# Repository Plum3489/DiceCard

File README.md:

# DiceCard

A buisiness-card-sized, battery-powered electronic dice roller :D 
Its build around the **ATtiny1614-SSN**, 10 LEDs, and a single button. 

## Instructions
1. Press to wake
2. short-press to pick a die
3. hold to roll
It goes back to sleep when it's done.

## Features

- 7 selectable dice  **d2, d4, d6, d8, d10**, plus two special modes:
  - **"1" -> d20**: two chained d10 rolls, LED-animated, you sum the results
  - **"9" -> d100**: tens-digit roll + units-digit roll (flat 1-100)
  - Deep sleep (power-down) between uses -> wakes only on button press
  - Only a single button

## Bill of materials (BOM)
| Amount | Part                        | Notes                                             | Price          | Links                                                                                                                                                                                                                                                                                                       |   |   |   |   |   |
|--------|-----------------------------|---------------------------------------------------|----------------|-------------------------------------------------------------------------------------------------------------------------------------------------------------------------------------------------------------------------------------------------------------------------------------------------------------|---|---|---|---|---|
| 1x     | ATtiny1614                  |                                                   | 1,05€          | https://www.reichelt.de/de/de/shop/produkt/8-bit-attiny_avr-risc_mikrocontroller_16_kb_20_mhz_soic-14-335590#closemodal                                                                                                                                                                                     |   |   |   |   |   |
| 1x     | Cap 0805, 1 µF              |                                                   | 0,08€          | https://www.reichelt.de/de/de/shop/produkt/mlcc_0805_1_f_16_v_x7r_-10_h1_25_mm-429214                                                                                                                                                                                                                       |   |   |   |   |   |
| 10x    | LED, SMD 0603 Red           |                                                   | 0,07€          | https://www.reichelt.de/de/de/shop/produkt/led_smd_0603_rot_56_mcd_100_-231657                                                                                                                                                                                                                              |   |   |   |   |   |
| 10x    | Resistor, SMD 0402 2,2 kOhm |                                                   | 0,02€          | https://www.reichelt.de/de/de/shop/produkt/smd-widerstand_0402_2_2_kohm_63_mw_1_-182934                                                                                                                                                                                                                     |   |   |   |   |   |
| 1x     | Cap 1206 100nF              |                                                   | 0,04€          | https://www.reichelt.de/de/de/shop/produkt/mlcc_1206_100_nf_100_v_-10_x7r-409241                                                                                                                                                                                                                            |   |   |   |   |   |
| 1x     | Battery Holder Ø 20 mm      |                                                   | 0,67€          | https://www.reichelt.de/de/de/shop/produkt/knopfzellenclip_fuer_20_mm_smd-74686                                                                                                                                                                                                                             |   |   |   |   |   |
| 1x     | UDPI-Programming Board      | IF NEEDED. ONLY ONE. YOU DONT NEED THEM PER BOARD | 7,50€          | https://www.berrybase.de/adafruit-updi-friend-3v-5v-stromversorgung-ch340e-chip-usb-c-3v-5v-1k-rueckkopplungswiderstand?gad_source=1&gad_campaignid=22696911352&gbraid=0AAAAADSQJK6ArylTule_RzYSf8CoHO8D9&gclid=CjwKCAjwqJXUBhBNEiwA8BgG7k4nVT0fIzVh1WPstvDr96SSSF5Iflz-FT8h6PRQLShXnonjbpDu8xoCaoEQAvD_BwE |   |   |   |   |   |
| 1x     | PCB                         |                                                   | ~4€            |                                                                                                                                                                                                                                                                                                             |   |   |   |   |   |
| Total  | ----------                  | ----------                                        | 6,74€ (+7,50€) |                                                                                                                                                                                                                                                                                                             |   |   |   |   |   |

## Pin Map
| Silkscreen label | ATtiny1614 pin | Function |
|---|---|---|
| D1 | PA2 | LED |
| D2 | PA3 | LED |
| D3 | PA4 | LED |
| D4 | PA5 | LED |
| D5 | PA6 | LED |
| D6 | PA7 | LED |
| D7 | PB3 | LED |
| D8 | PB2 | LED |
| D9 | PB1 | LED |
| D10 | PB0 | LED |
| — | PA1 | Button (to GND, internal pull-up) |
| — | PA0 | UPDI (programming only) |
| — | VCC | CR2032 + |
| — | GND | CR2032 − |

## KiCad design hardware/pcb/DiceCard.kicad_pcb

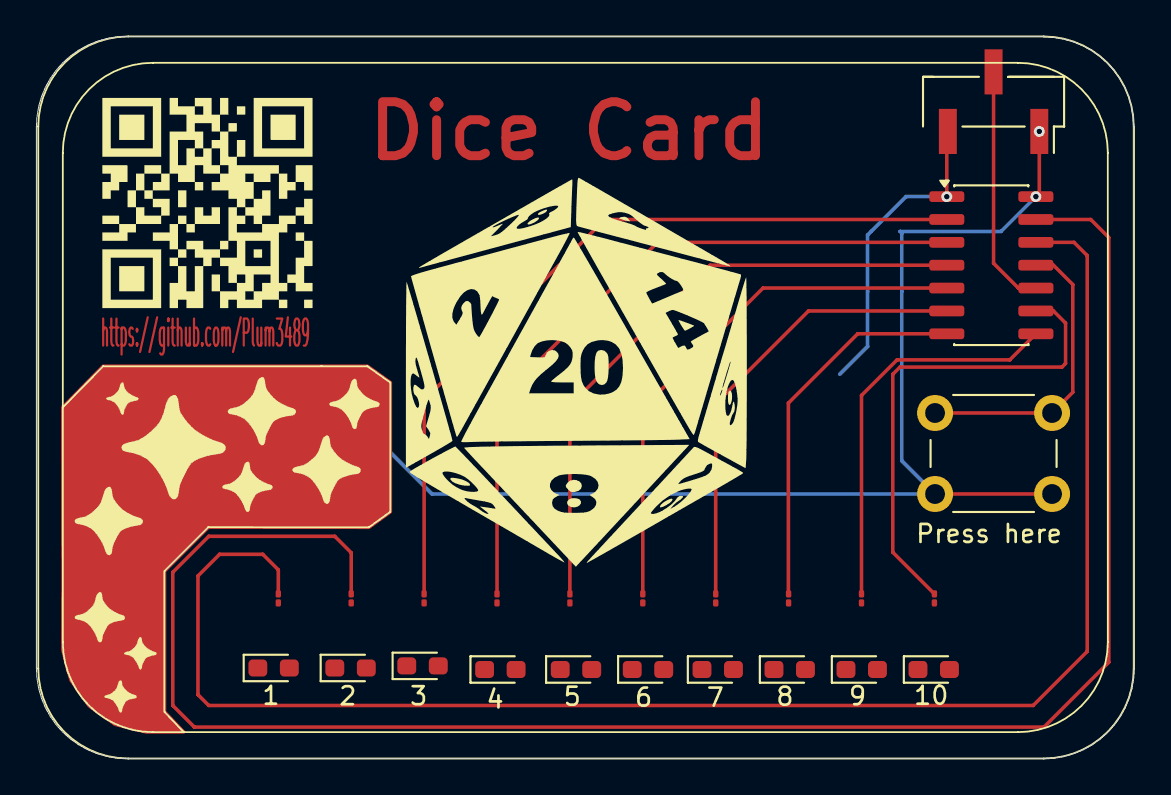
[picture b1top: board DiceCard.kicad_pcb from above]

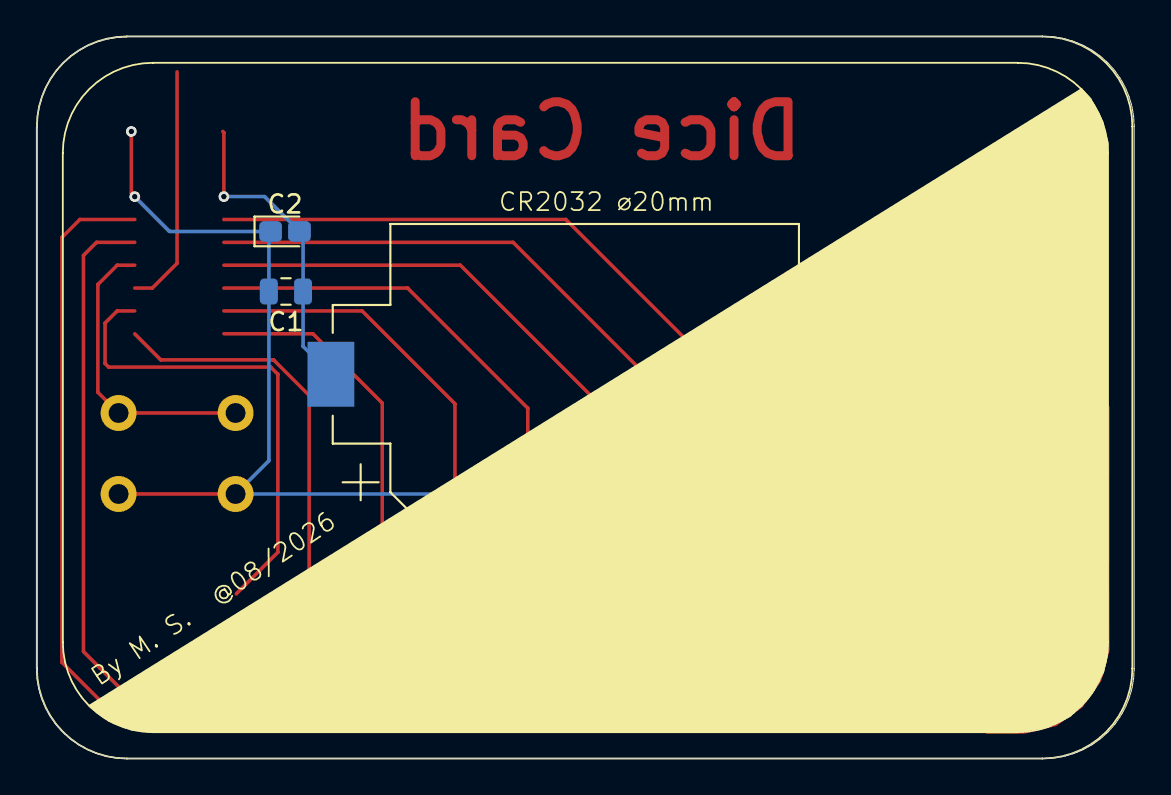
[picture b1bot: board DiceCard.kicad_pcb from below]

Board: 2 copper layers, 61.0 x 40.1 mm, 26 parts (3 on the bottom side), 24 nets.

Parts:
1, 2, 3, 4, 5, 6, 7, 8, 9, 10: LED; LED_0603_1608Metric_Pad1.05x0.95mm_HandSolder
BT1: Battery_Cell; BatteryHolder_Keystone_1060_1x2032
C1: 100nF; C_0805_2012Metric
C2: 1µF; CP_EIA-1608-08_AVX-J_HandSolder
J1: Conn_01x03_Pin; PinHeader_1x03_P2.54mm_Vertical_SMD_Pin1Right
Press here: SW_Push; SW_PUSH_6mm
R1, R2, R3, R4, R5, R6, R7, R8, R9, R10: 2.2kΩ; R_01005_0402Metric
U1: ATtiny1614-SS; SOIC-14_3.9x8.7mm_P1.27mm

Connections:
unnamed: BT1.1 (+), C1.1, C2.2, J1.3, U1.1 (VCC)
unnamed: 1.1 (K), 2.1 (K), 3.1 (K), 4.1 (K), 5.1 (K), 6.1 (K), 7.1 (K), 8.1 (K), 9.1 (K), 10.1 (K), BT1.2 (-), C1.2, C2.1, J1.1, Press here.2, U1.14 (GND)
unnamed: 1.2 (A), R1.2
unnamed: 2.2 (A), R2.2
unnamed: 3.2 (A), R3.2
unnamed: 4.2 (A), R4.2
unnamed: 5.2 (A), R5.2
unnamed: 6.2 (A), R6.2
unnamed: 7.2 (A), R7.2
unnamed: 8.2 (A), R8.2
unnamed: 9.2 (A), R9.2
unnamed: 10.2 (A), R10.2
unnamed: J1.2, U1.10 (~RESET/PA0)
unnamed: Press here.1, U1.11 (PA1)
unnamed: R1.1, U1.12 (PA2)
unnamed: R2.1, U1.13 (PA3)
unnamed: R3.1, U1.2 (PA4)
unnamed: R4.1, U1.3 (PA5)
unnamed: R5.1, U1.4 (PA6)
unnamed: R6.1, U1.5 (PA7)
unnamed: R10.1, U1.9 (PB0)
unnamed: R9.1, U1.8 (PB1)
unnamed: R8.1, U1.7 (PB2)
unnamed: R7.1, U1.6 (PB3)

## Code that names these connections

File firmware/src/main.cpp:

/*
      DiceCard - ATtiny1614-SSN
-------------------------------------

Code for my Dice Card, first time using the chip itself instead of a microcontroller board :P

PIN MAP:
    D1  = PA2      D6  = PA7
    D2  = PA3      D7  = PB3
    D3  = PA4      D8  = PB2
    D4  = PA5      D9  = PB1
    D5  = PA6      D10 = PB0
    Button = PA1 (button to GND, internal pull-up, active LOW)
    PA0 = UPDI (not used as GPIO)
*/




#include <Arduino.h>
#include <avr/sleep.h>
#include <avr/interrupt.h>

#define D100_TENS_UNITS METHOD true

const uint16_t LONG_PRESS_MS = 550;
const uint16_t DEBOUNCE_MS = 25;

// Pins
const uint8_t ledPins[10] = {
  PIN_PA2, // D1
  PIN_PA3, // D2
  PIN_PA4, // D3
  PIN_PA5, // D4
  PIN_PA6, // D5
  PIN_PA7, // D6
  PIN_PB3, // D7
  PIN_PB2, // D8
  PIN_PB1, // D9
  PIN_PB0  // D10
};
const uint8_t BTN = PIN_PA1;

// Selectable Die
const uint8_t dieOptions[7] = {1, 2, 4, 6, 8, 9, 10};
const uint8_t NUM_OPTIONS = 7;

// Methods

void allOff(){
  for(uint16_t i = 0; i<10; i++) digitalWrite(ledPins[i], LOW);
}

void allOn(){
  for(uint16_t i = 0; i<10; i++) digitalWrite(ledPins[i], HIGH);
}

void lightOnly(uint8_t idx){
  for (uint8_t i = 0; i < 10; i++) digitalWrite(ledPins[i], i == idx ? HIGH : LOW);
}

bool buttonPressed(){
  return digitalRead(BTN) == LOW;
}

void waitForPressStart(){ while (!buttonPressed()) { /* spin */ }
  delay(DEBOUNCE_MS);
  while (!buttonPressed()) { /* debounce glitch, keep waiting */ }
}

// Blocks until either the button is released before LONG_PRESS MS -> returns false
// or the hold time reaches LONG_PRESS_MS -> returns true immediately
bool waitForPressOutcome() {
  waitForPressStart();
  uint32_t start = millis();
  while (buttonPressed()) {
    if (millis() - start >= LONG_PRESS_MS) {
      return true; // long press threshold reached -> go roll now
    }
  }
  delay(DEBOUNCE_MS);
  return false; // released early -> short press
}

// sleepy eepy
volatile bool wokeUp = false;

void wakeISR(){
  wokeUp = true;
}

void goToSleep() {
  allOff();
  wokeUp = false;

  attachInterrupt(digitalPinToInterrupt(BTN), wakeISR, FALLING);

  set_sleep_mode(SLEEP_MODE_PWR_DOWN);
  cli();
  sleep_enable();
  sei();
  sleep_cpu();      // <-- CPU halts here until button press wakes it, because energy saving :>
  sleep_disable();

  detachInterrupt(digitalPinToInterrupt(BTN));

  // debounce the waking press, then wait for it to be released
  // before we start listening for menu presses.
  delay(DEBOUNCE_MS);
  while (buttonPressed()) { /* wait out the wake press */ }
  delay(DEBOUNCE_MS);
}

// Animations
// Rolls a "faces"-sided die, declaring the chase.
// goes to the result and holds 2 secs. Then it turns off.
uint8_t rollAndShow(uint8_t faces) {
  uint8_t resultIdx = random(0, faces); // 0..faces-1

  const uint8_t loops = 3; // full spins before landing
  uint16_t totalSteps = (uint16_t)loops * faces + resultIdx + 1;

  for (uint16_t i = 0; i < totalSteps; i++) {
    uint8_t idx = i % faces;
    lightOnly(idx);

    uint16_t remaining = totalSteps - i;
    uint16_t d = map(remaining, 1, totalSteps, 220, 35); // decelerate
    delay(d);
  }

  lightOnly(resultIdx);
  delay(2000);
  allOff();

  return resultIdx + 1;
}

void performRoll(uint8_t dieCode){
  if(dieCode == 1){
    // Special case d20 -> two d10s, youre gonna read the sum
    rollAndShow(10);
    delay(150);
    rollAndShow(10);
  }else if (dieCode == 9) {
    #if D100_TENS_UNITS_METHOD
        // SPECIAL: d100 => tens-digit roll (0-9, shown as faces 1-10 wher
        rollAndShow(10);
        delay(150);
        rollAndShow(10);
    #else
        // literal spec: two d10 rolls, reader adds them together
        rollAndShow(10);
        delay(150);
        rollAndShow(10);
    #endif
      } else {
        // normal die: dieCode itself is the number of faces
        rollAndShow(dieCode);
      }
}

// Setup and loop
void setup(){
  for(uint8_t i = 0; i < 10 ; i++) pinMode(ledPins[i], OUTPUT);
  allOff();
  pinMode(BTN, INPUT_PULLUP);
}

void loop(){
  goToSleep();
  randomSeed(micros());

  allOn();
  delay(600);
  allOff();
  delay(150);

  // Selection "menu"-thing
  uint8_t selection = 0;
  while(true){
      lightOnly(selection); // show current with corresponding LED
    bool longPress = waitForPressOutcome();

    if (longPress) {
      break; // hold -> roll this die now
    } else {
      selection = (selection + 1) % NUM_OPTIONS; // short press -> next option
    }
  }

  allOff();
  delay(150);

  // roll this thing :D
  performRoll(dieOptions[selection]);

  // loops back to Sleep
}
